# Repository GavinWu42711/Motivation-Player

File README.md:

# Motivation Player
An MP3-like player where WAV files of "motivational" quotes can be played from an SD card

**(Link to see it in action -> https://youtube.com/shorts/U501b-Ut6_k)**

# Motivation
I wanted to create this project as a way to learn how to make PCB's and design in CAD with minimal help from tutorials. I also often struggle with motivation and fall into the cyclical loop of "negative thoughts" so this project is meant to help break that if I'm having a bad day

# Features
- 128 x 64 OLED display to show information about what's being played
- A 30mm speaker with an LM386 audio amplifier to play sound at good quality
- Rotary encoder to scroll between quotes
- Potentiometer to adjust volume
- 2 Buttons to play quotes and randomize quotes
- Power switch to turn on and off the project (to save battery)
- SD card module to hold many recordings (Assuming ~2 mb per .WAV file, roughly 64 recordings on an 128 mb SD card)

# How It Works
Using SPI, the Pi Pico reads the .WAV files from the SD card module. Each file is named with an index (i.e 0.wav, 1.wav, e.t.c) for simplicity. Extra information about the file -- such as the name of the person who made the audio -- are stored in txt files named similarly. The Pi Pico then uses PWM to mimic DAC, with an extra capacitor and potentiometer to smooth it out. Finally, the audio passes through an LM386 audio amplifier before reaching the speaker. The LM386 was chosen due to not needing a heat sink (saving space) while still providing good quality audio. Information about the audio being played is displayed on a 128 x 64 SSD1306 through I2C. This display was chosen due to having a smaller form factor and easy to read text.

# CAD Model
The enclosure for the PCB is comprised of a bottom and a lid. The two screw together with M2 screws in each of the corner (4 total). All the parts were designed using Fusion.

**Lid**

**Bottom**

**Fully Assembled**

*Some parts such as the switch, speaker, and potentiometer are slightly off due to not having models for the ones to be used in the project. The placeholders are a way to show proof of concept*

# PCB
The PCB was designed using KiCAD. All the parts were chosen to be through hole instead of surface mount for easier soldering.

**Schematic**

**PCB**

*C5 is supposed to be a non-polarized capacitor*

**Soldered PCB**

# Firmware
Circuit Python was used to program the project as it interfaces best with the many pins of the Raspberry Pi Pico. Libraries from Adafruit were also used to interface with the OLED. The program can only read .WAV files from the SD card, with the SD card being formatted in FAT32 and the .WAV files being mono-channel, 16-bit, 22kHz.

The "lib" folder in the "Firmware" folder contains the library files that need to be uploaded to the Pi Pico in addition to the code and Circuit Python. These imports include "adafruit_display_text" and "adafruit_displayio_ssd1306". Other imports are part of Circuit Python.

# BOM
- 1 Raspberry Pi Pico
- 1 rotary encoder
- 1 potentiometer
- 1 SSD1306 (128 x 64)
- 1 micro SD card module
- 2 push buttons
- 1 SPST switch
- 1 3xAA battery holder module
- 1 LM3886
- 1 30mm speaker
- 1 0.05 uF (50 nF) capacitor (non-polarized)
- 1 10 uF capacitor (polarized)
- 1 10 uF capacitor (non-polarized)
- 2 100 uF capacitors (polarized)
- 1 250 uF capacitor (polarized)
- 3 AA batteries
- 1 SD card (any size works)
- Pinheaders
- 3D printed enclosure
- PCB
- 4 M2 Screws

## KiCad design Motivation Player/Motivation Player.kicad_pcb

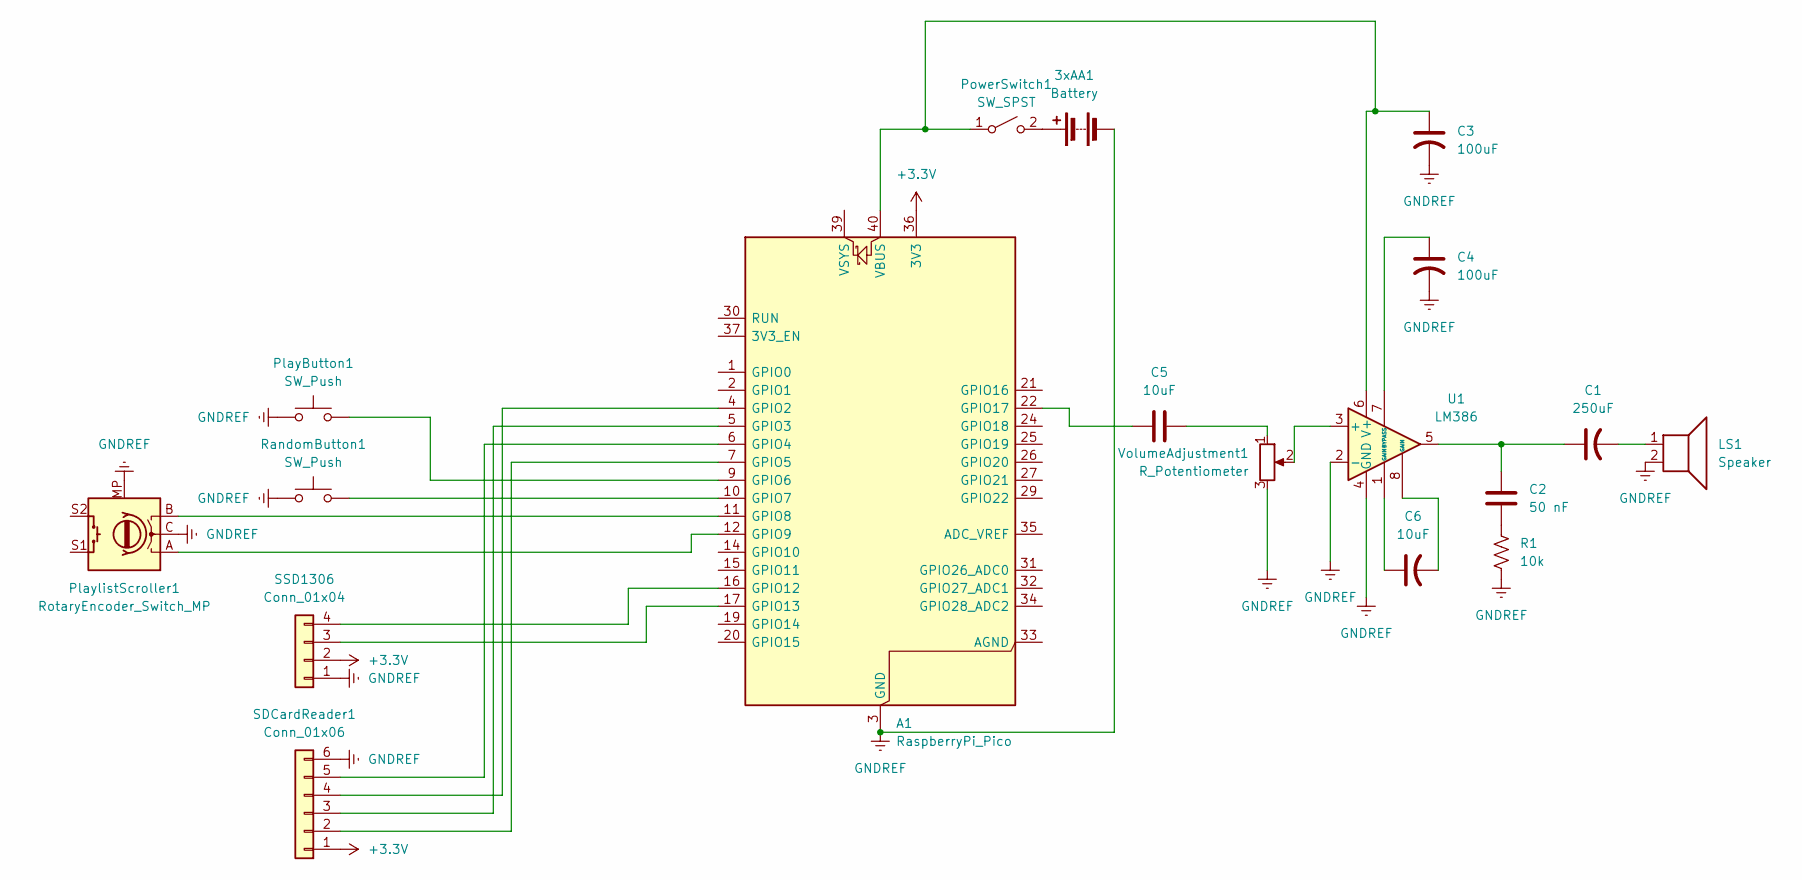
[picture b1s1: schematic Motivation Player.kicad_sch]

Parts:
3xAA1: Battery; BatteryHolder_TruPower_BH-331P_3xAA
A1: RaspberryPi_Pico; RaspberryPi_Pico_Common_THT
C1: 250uF; CP_Radial_D6.3mm_P2.50mm
C2: 50 nF; C_Disc_D5.0mm_W2.5mm_P5.00mm
C3, C4: 100uF; CP_Radial_D5.0mm_P2.50mm
C5, C6: 10uF; CP_Radial_D5.0mm_P2.50mm
LS1: Speaker; SolderWire-0.1sqmm_1x02_P3.6mm_D0.4mm_OD1mm_Relief
PlayButton1: SW_Push; SW_PUSH-12mm
PlaylistScroller1: RotaryEncoder_Switch_MP; RotaryEncoder_Alps_EC11E-Switch_Vertical_H20mm
PowerSwitch1: SW_SPST; SolderWire-0.1sqmm_1x02_P3.6mm_D0.4mm_OD1mm_Relief
R1: 10k; R_Axial_DIN0207_L6.3mm_D2.5mm_P10.16mm_Horizontal
RandomButton1: SW_Push; SW_PUSH-12mm
SDCardReader1: Conn_01x06; PinHeader_1x06_P2.54mm_Vertical
SSD1306: Conn_01x04; PinHeader_1x04_P2.54mm_Vertical
U1: LM386; DIP-8_W7.62mm_Socket
VolumeAdjustment1: R_Potentiometer; Potentiometer_Piher_PT-10-V10_Vertical

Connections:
+3.3V: A1.36 (3V3), SDCardReader1.1, SSD1306.2
GNDREF: 3xAA1.2 (-), A1.3 (GND), A1.8 (GND), A1.13 (GND), A1.18 (GND), A1.23 (GND), A1.28 (GND), A1.38 (GND), C3.2, C4.2, LS1.2, PlayButton1.1, PlaylistScroller1.C, PlaylistScroller1.MP, R1.2, RandomButton1.1, SDCardReader1.6, SSD1306.1, U1.2 (-), U1.4 (GND), VolumeAdjustment1.3; also elsewhere on the board
unnamed: 3xAA1.1 (+), PowerSwitch1.2 (B)
unnamed: A1.4 (GPIO2), SDCardReader1.4
unnamed: A1.5 (GPIO3), SDCardReader1.3
unnamed: A1.6 (GPIO4), SDCardReader1.5
unnamed: A1.7 (GPIO5), SDCardReader1.2
unnamed: A1.9 (GPIO6), PlayButton1.2
unnamed: A1.10 (GPIO7), RandomButton1.2
unnamed: A1.11 (GPIO8), PlaylistScroller1.B
unnamed: A1.12 (GPIO9), PlaylistScroller1.A
unnamed: A1.16 (GPIO12), SSD1306.4
unnamed: A1.17 (GPIO13), SSD1306.3
unnamed: A1.22 (GPIO17), C5.1
unnamed: A1.40 (VBUS), C3.1, PowerSwitch1.1 (A), U1.6 (V+)
unnamed: C1.1, C2.1, U1.5
unnamed 16: C1.2, LS1.1; also elsewhere on the board
unnamed: C2.2, R1.1
unnamed: C5.2, VolumeAdjustment1.1
unnamed: C6.1, U1.1 (GAIN)
unnamed: C6.2, U1.8 (GAIN)
unnamed: U1.3 (+), VolumeAdjustment1.2
unnamed: C4.1, U1.7 (BYPASS)

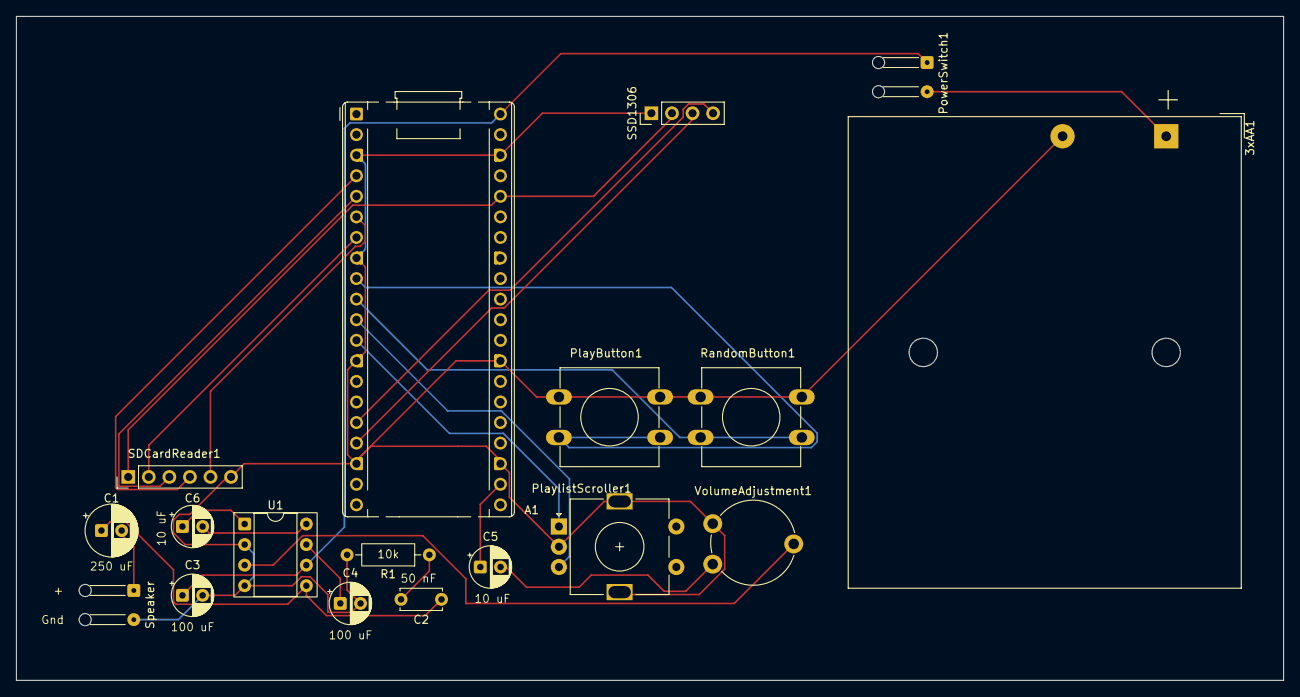
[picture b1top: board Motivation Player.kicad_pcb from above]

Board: 2 copper layers, 156.5 x 82.0 mm, 18 parts (0 on the bottom side), 23 nets.

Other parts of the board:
Speaker: Speaker; SolderWire-0.1sqmm_1x02_P3.6mm_D0.4mm_OD1mm_Relief

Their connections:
GNDREF: Speaker.2; also elsewhere on the board
unnamed 16: Speaker.1; also elsewhere on the board
